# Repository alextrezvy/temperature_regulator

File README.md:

Thermo-couple-based temperature regulator allows to maintain near-constant temperature by automatically turning a resistive load on and off.
Can be used in soldering irons, electric ovens, etc. A thermo-couple must be electrically isolated from metal parts, as it has no galvanic isolation from the power line.

The original schematics was published at the forums VRTP:
https://vrtp.ru/index.php?s=1665539694ef7bbe652402ec1cce5775&showtopic=24903&st=0

Sources are made in KiCAD 5.1.4.

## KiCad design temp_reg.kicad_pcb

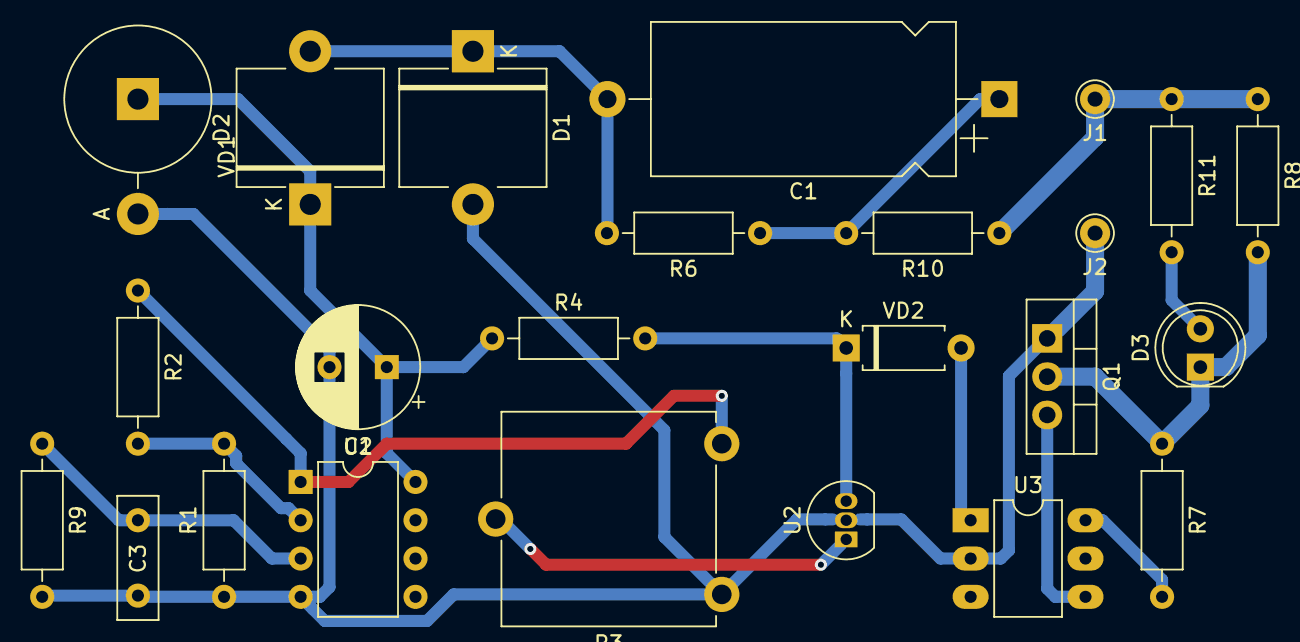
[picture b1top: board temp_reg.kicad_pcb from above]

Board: 2 copper layers, 24 parts (0 on the bottom side), 15 nets.

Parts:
C1: 1mk; CP_Axial_L20.0mm_D10.0mm_P26.00mm_Horizontal
C2: 220mk; CP_Radial_D8.0mm_P3.80mm
C3: 100n; C_Disc_D8.0mm_W2.5mm_P5.00mm
D1, D2: D; D_5KP_P10.16mm_Horizontal
D3: LED; LED_D5.0mm
J1, J2: Conn_01x01; Pin_D1.0mm_L10.0mm
Q1: BT136-600; TO-220-3_Vertical
R1: 1.5k; R_Axial_DIN0207_L6.3mm_D2.5mm_P10.16mm_Horizontal
R2, R6: 1M; R_Axial_DIN0207_L6.3mm_D2.5mm_P10.16mm_Horizontal
R3: 20k; Potentiometer_ACP_CA14V-15_Vertical
R4: 1k; R_Axial_DIN0207_L6.3mm_D2.5mm_P10.16mm_Horizontal
R7: 10k; R_Axial_DIN0207_L6.3mm_D2.5mm_P10.16mm_Horizontal
R8: Heater; R_Axial_DIN0207_L6.3mm_D2.5mm_P10.16mm_Horizontal
R9, R10: 10; R_Axial_DIN0207_L6.3mm_D2.5mm_P10.16mm_Horizontal
R11: 470k; R_Axial_DIN0207_L6.3mm_D2.5mm_P10.16mm_Horizontal
U1: LM358; DIP-8_W7.62mm
U2: TL431LP; TO-92_Inline
U3: MOC3062M; DIP-6_W7.62mm_LongPads
VD1: кс512; D_5KP_P7.62mm_Vertical_AnodeUp
VD2: 3V; D_A-405_P7.62mm_Horizontal

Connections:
GND: C2.2, C3.2, D1.2, J2.1, Q1.1, R1.1, R3.3, R9.2, U1.4, U2.2, U3.2, VD1.2
unnamed: C1.1, R6.1, R10.2
unnamed: C1.2, D1.1, D2.2, R6.2
unnamed: C2.1, D2.1, R4.1, U1.8, VD1.1
unnamed: C3.1, R9.1, U1.3
unnamed: D3.1, Q1.2, R7.1, R8.2
unnamed: D3.2, R11.2
unnamed: J1.1, R8.1, R10.1, R11.1
unnamed: Q1.3, U3.4
unnamed: R1.2, R2.2, U1.2
unnamed: R2.1, R3.1, U1.1
unnamed: R3.2, U2.1
unnamed: R4.2, U2.3, VD2.1
unnamed: R7.2, U3.6
unnamed: U3.1, VD2.2

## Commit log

2020-02-19 initial placement of finished and tested pcb and schematics
2020-02-19 README file added
